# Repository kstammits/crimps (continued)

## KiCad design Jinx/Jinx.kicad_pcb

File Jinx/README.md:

# crimps
 Mutated Kinks = Karltron Crimps

Originally cloning Mutable Instruments' Kinks
https://github.com/pichenettes/eurorack
Transferring from EAGLE to KiCad and updating from 0402 to 0805 construction means basically the whole thing is rewritten from scratch. The PCB is therefore unrelated to Kinks: Crimps is a karltron design 2021. 

Info on karltron.com/crimps

it's cc-by-sa so copyleft

On the internet forums, someone else has mentioned started a THT version, asking about it but not shared yet because reasons. 
https://modwiggler.com/forum/viewtopic.php?p=3644155

signal diode:
FDLL4148 is D1206

changing pinout on transistors, to SOT-23. so DO BE CAREFUL AND RECHECK THE PINOUT  (note v101 has the transistors on upside down, v122 is fixed)

layout looking fine in 0805

The S&H calls for a fancy C0G capacitor and OPA4171 opamp. We'll try it with a plain capacitor and TL074, which are compatible, but expect poor performance. I'm curious how poor, if it's acceptable we can save $$. Will try both, and report back here. But v101 is otherwise broken so 

when the input looks like noise at >9vpp, which is normal, the trigger goes off for successivly lower notes. feels like an accumulating towards -7.5Volts. Input values lower than -7V till self trigger If something softer is in the input, or values <7 volts absolute it will not self-trigger.  i think i need to add a capacitor somewhere or redo the ground plane.  Anytime the input sinks below -7V it pulls on the gate. Not sure it's really triggering, would need a two-channel scope to see if they coincide.  

if you keep the input above -7V, then the vgs doesn't trigger and everything is good. So I should just reduce the noise volume, the original kinks was showing just about +/-5V, and 10vpp is enough noise. mine's doing like 19vpp noise, and catching a very brief acquisition during noise spikes under -7V. 

so actually it works fine. i should/need/to/ reduce the noise volume to 10vpp to avoid the -7V issue. That's fixed by changing R27 from a 1.5M as originally given to a 1M. Now the noise is only +/-6V and everything works. then of course flip the transistors right-side-up. I've tested with only a J112 THT jfet tacked on crooked.  

Testing another JFET as replacement; the MMBFJ201 (marked 6P) is not great. Sort of works, sort of doesnt. The trigger time is not sufficient for acquisition, so each trigger can only move the sample by a few volts, and swinging +/-10V will need 2,3,4,5 triggers. Also, when the input is quite low the sample drains without triggers, so the J201 seems to have some leakage Igs as well as a higher Rds-on vs the J112. The incomplete-acquisitions problem might be okay for your use, but it really reduces the output range when the internal noise source is +/-6V and each trigger seems to only change the value to +/-1V. 

Testing the MMBF4392 (marked 6K)
Holds nicely down to -7.5V then drops, as others do, because my gate off voltage is -11, so less than four difference causes a sampling.   Seems to be working well. 

Testing the MMBFJ112 (marked 6R) last since a THT J112 was working well. Also seems to perform adequately. 
 
During hold testing, discovered unplugging and replugging the output causes a drop in the sample; perhaps this is caused by the brief short to ground pulling on the opamp. Additional decoupling caps did not help, looks like the OPA4171 final out buffer loses some state through the 180R output. Another output stage might be required to separate the held voltage from the output buffer. That's not fixable without additional chips.

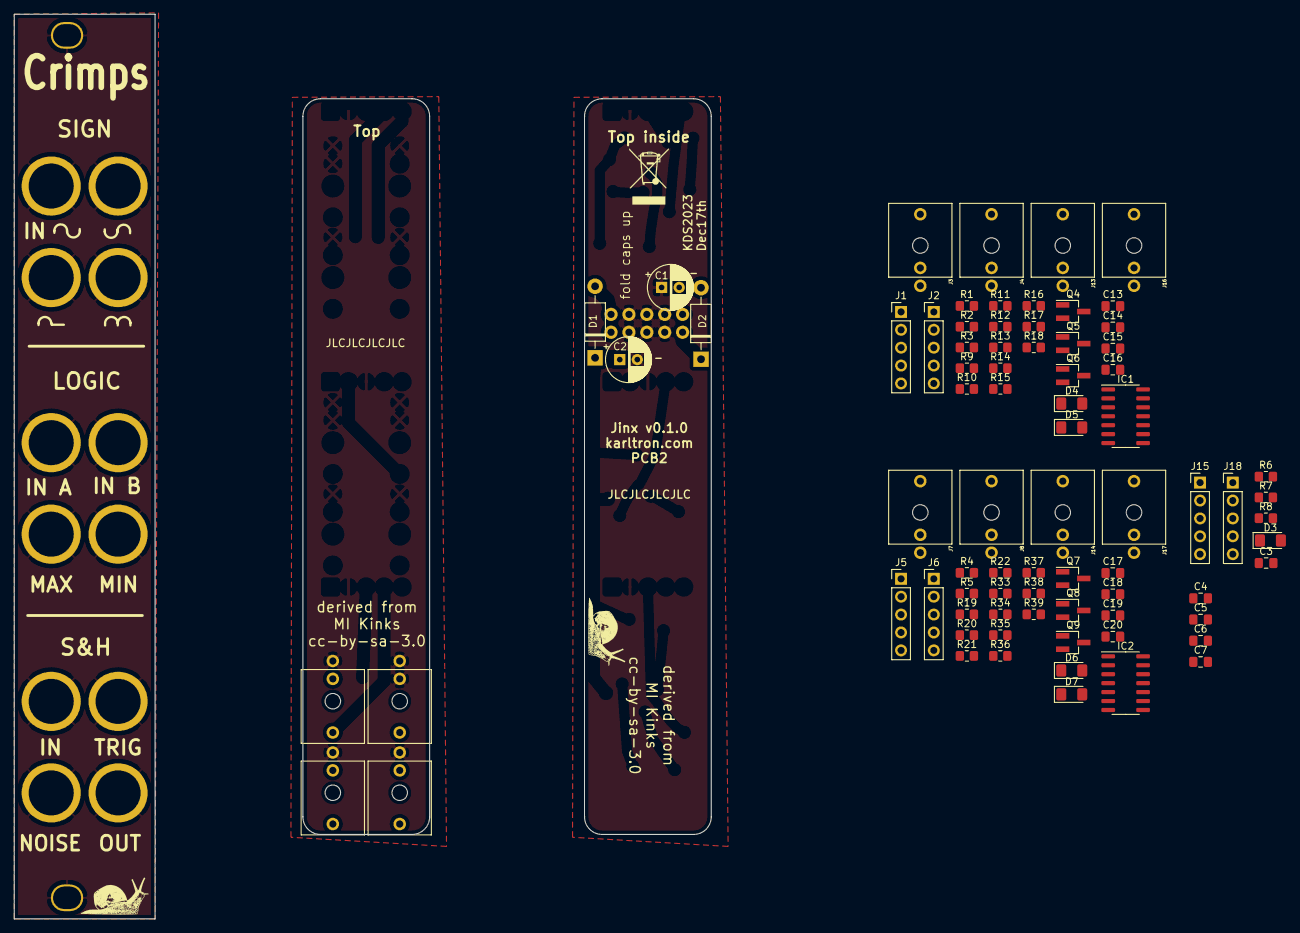
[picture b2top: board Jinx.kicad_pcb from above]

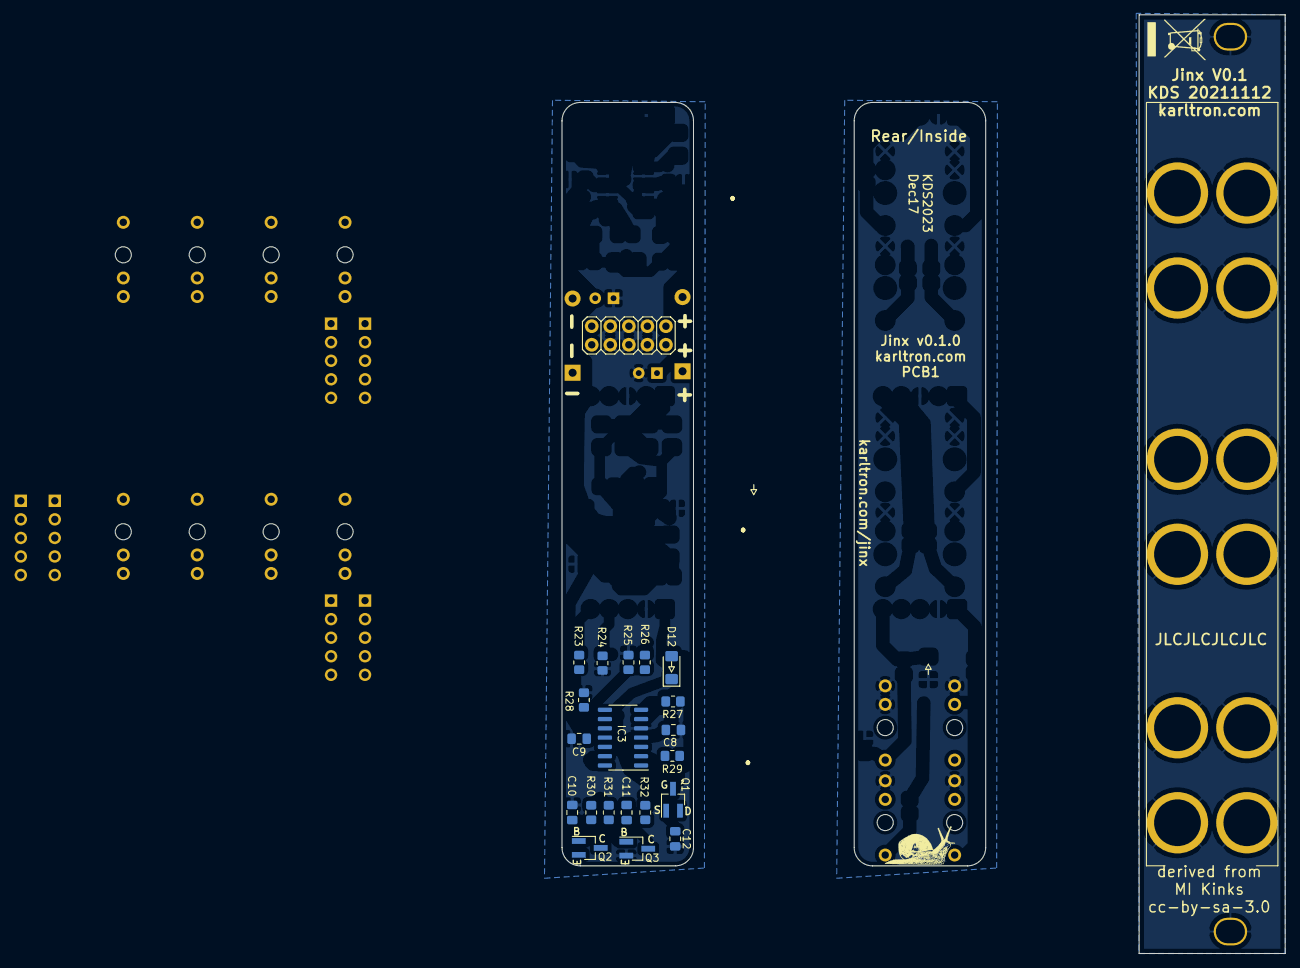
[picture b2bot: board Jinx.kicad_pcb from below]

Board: 2 copper layers, 113 parts (21 on the bottom side), 55 nets, no tracks yet.

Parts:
C1, C2: 22u; CP_Radial_D6.3mm_P2.50mm
C3, C16, C20: 100p; C_0805_2012Metric_Pad1.18x1.45mm_HandSolder
C4, C5, C6, C7, C8, C9, C11, C13, C17: 100n; C_0805_2012Metric_Pad1.18x1.45mm_HandSolder
C10, C14, C18: 4.7u; C_0805_2012Metric_Pad1.18x1.45mm_HandSolder
C12, C15, C19: 10n; C_0805_2012Metric_Pad1.18x1.45mm_HandSolder
D1, D2: S1JL; D_DO-41_SOD81_P10.16mm_Horizontal
D3, D4, D5, D6, D7, D12: 1N4148; D_1206_3216Metric_Pad1.42x1.75mm_HandSolder
G1: Logo_Open_Hardware_Small; snail4.sm
H1, H14: MountingHole_Pad; SLOT-1
H2, H2#2, H2#3, H2#4, H2#5, H2#6, H2#7, H2#8, H2#9: J1; MountingHole_6.4mm_M6_Pad
H6, H6#2, H6#3: J2; MountingHole_6.4mm_M6_Pad
IC1, IC2, IC3: TL074; SOIC-14_3.9x8.7mm_P1.27mm
J1, J5, J18: Conn_01x05_Male; PinHeader_1x05_P2.54mm_Vertical
J2, J6, J15: Conn_01x05_Female; PinHeader_1x05_P2.54mm_Vertical
J3, J4, J7, J8, J9, J10, J11, J12, J13, J14, J16, J17: PJ301_THONKICONN6; WQP_PJ_301M6
JP1: M05X2PTH; AVR_ICSP
Q1, Q6, Q9: MMBFJ309; SOT-23_Handsoldering
Q2, Q3, Q4, Q5, Q7, Q8: MMBT3904; SOT-23_Handsoldering
R1, R4, R30: 470k; R_0805_2012Metric_Pad1.20x1.40mm_HandSolder
R2, R5, R31: 4.7k; R_0805_2012Metric_Pad1.20x1.40mm_HandSolder
R3, R19, R27: 470K; R_0805_2012Metric_Pad1.20x1.40mm_HandSolder
R6, R8, R10, R11, R21, R22: 180; R_0805_2012Metric_Pad1.20x1.40mm_HandSolder
R7, R9, R16, R17, R20, R28, R32, R37, R38: 100k; R_0805_2012Metric_Pad1.20x1.40mm_HandSolder
R12, R13, R14, R24, R26, R29, R33, R34, R35: 1.0M; R_0805_2012Metric_Pad1.20x1.40mm_HandSolder
R15, R18, R23, R25, R36, R39: 10k; R_0805_2012Metric_Pad1.20x1.40mm_HandSolder

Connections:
GND: C1.1, C2.2, C4.1, C5.2, C6.2, C7.1, C8.2, C9.1, C10.2, C12.2, C14.2, C15.2, C18.2, C19.2, D3.2 (A), D5.2 (A), D7.2 (A), H1.1, H2.1, H2#2.1, H2#3.1, H2#4.1, H2#5.1, H2#6.1, H2#7.1, H2#8.1, H2#9.1, H6.1, H6#2.1, H6#3.1, H14.1, IC1.5 (+), IC2.5 (+), IC3.5 (+), J1.2, J2.2, J3.P1 (1), J4.P1 (1), J5.2, J6.2, J7.P1 (1), J8.P1 (1), J9.P1 (1), J10.P1 (1), J10.P2 (2), J11.P1 (1), J12.P1 (1), J13.P1 (1), J14.P1 (1), J15.2, J16.P1 (1), J16.P2 (2), J17.P1 (1), J17.P2 (2), J18.2, JP1.3, JP1.4, JP1.5, JP1.6, JP1.7, JP1.8, Q3.2 (E), Q5.2 (E), Q8.2 (E), R7.1, R13.2, R16.1, R17.1, R18.1, R24.2, R25.1, R28.1, R34.2, R37.1, R38.1, R39.1
unnamed: C11.2, R32.2
unnamed: C13.2, R9.2
unnamed: C17.2, R20.2
unnamed: D1.2 (A), JP1.1, JP1.2
unnamed: D2.1 (K), JP1.9, JP1.10
unnamed: D4.2 (A), Q6.3 (G), R12.1
unnamed: D4.1 (K), IC1.8
unnamed: D6.2 (A), Q9.3 (G), R33.1
unnamed: D6.1 (K), IC2.8
unnamed: D12.2 (A), Q1.3 (G), R29.1
unnamed: D12.1 (K), IC3.8
unnamed: IC1.1, IC1.2 (-), Q6.2 (D), R12.2
unnamed: IC1.6 (-), R3.2, R9.1
unnamed: IC1.10 (+), R15.2, R17.2
unnamed: IC1.9 (-), R14.1, R18.2
unnamed: C15.1, IC1.12 (+), Q6.1 (S)
unnamed: IC2.1, IC2.2 (-), Q9.2 (D), R33.2
unnamed: IC2.6 (-), R19.2, R20.1
unnamed: IC2.10 (+), R36.2, R38.2
unnamed: IC2.9 (-), R35.1, R39.2
unnamed: C19.1, IC2.12 (+), Q9.1 (S)
unnamed: IC3.1, IC3.2 (-), Q1.2 (D), R29.2
unnamed: IC3.6 (-), R27.2, R32.1
unnamed: IC3.10 (+), R23.2, R28.2
unnamed: IC3.9 (-), R25.2, R26.1
unnamed: C12.1, IC3.12 (+), Q1.1 (S)
unnamed: J4.P3 (3), R11.1
unnamed: J8.P3 (3), R22.1
unnamed: C3.1, J10.P3 (3), R7.2
unnamed: J9.P2 (2), J11.P3 (3), R6.1
unnamed: J12.P3 (3), R8.1
unnamed: J3.P3 (3), J13.P2 (2), R10.1
unnamed: J7.P3 (3), J14.P2 (2), R21.1
unnamed: C16.1, J16.P3 (3), R16.2
unnamed: C20.1, J17.P3 (3), R37.2
unnamed: Q2.1 (B), Q3.1 (B)
unnamed: C10.1, Q2.2 (E), R30.2
unnamed: C11.1, Q3.3 (C), R31.1
unnamed: Q4.1 (B), Q5.1 (B)
unnamed: C14.1, Q4.2 (E), R1.2
unnamed: C13.1, Q5.3 (C), R2.1
unnamed: Q7.1 (B), Q8.1 (B)
unnamed: C18.1, Q7.2 (E), R4.2
unnamed: C17.1, Q8.3 (C), R5.1
NoiseB: IC1.7, IC2.7, IC3.7, J2.1, J6.1, J15.1, R3.1, R19.1, R27.1
NoiseT: J1.1, J5.1, J18.1, R6.2, R10.2, R21.2
SHInB: IC1.3 (+), IC2.3 (+), IC3.3 (+), J2.4, J6.4, J15.4, R13.1, R24.1, R34.1
SHInT: J1.4, J5.4, J9.P3 (3), J13.P3 (3), J14.P3 (3), J18.4
SHOutB: IC1.13 (-), IC1.14, IC2.13 (-), IC2.14, IC3.13 (-), IC3.14, J2.3, J6.3, J15.3
SHOutT: J1.3, J5.3, J18.3, R8.2, R11.2, R22.2
TrigInB: J2.5, J6.5, J15.5, R15.1, R23.1, R36.1
TrigInT: C3.2, C16.2, C20.2, D3.1 (K), D5.1 (K), D7.1 (K), J1.5, J5.5, J18.5
VCC: C2.1, C5.1, C6.1, C8.1, D1.1 (K), IC1.4 (V+), IC2.4 (V+), IC3.4 (V+), R1.1, R2.2, R4.1, R5.2, R14.2, R26.2, R30.1, R31.2, R35.2
VEE: C1.2, C4.2, C7.2, C9.2, D2.2 (A), IC1.11 (V-), IC2.11 (V-), IC3.11 (V-)

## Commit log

2021-11-18 initial
    upload of k2, derived from eagle and rewritten fully Crimps v1.0.1. Initial board prototype!
2021-11-18 adding screenshots
2021-11-19 v101 to order
    tweaks
2021-11-19 adding BOM
2021-11-19 Create BOM.Guide.xlsx
    nicer to read BOM
2021-12-13 dec2021
    status after testing v101
    found errors in this board
2021-12-13 ignore bak
2021-12-14 notes
2021-12-15 upd to board 1.2
    should fix transistor footprint and shift diodes
2021-12-16 versioning
    nudge traces
2021-12-16 printing pretty schem
2021-12-17 bomguide
2021-12-21 update for noise level
2022-02-01 ibom
    move files and add an ibom.html
2022-02-01 rename file
    regenerate
2022-02-02 logo added
    adding WEEE wheelie bin
2023-12-18 versioning
    kicad upd tweaks
2023-12-18 Shift Files
    Sorry we have to move a lot of files to add another board
2023-12-18 setup
2023-12-18 adding Jinx as a subfolder
2023-12-18 dont need those
2024-08-27 update bom and version
